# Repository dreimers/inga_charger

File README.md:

# inga_charger
Small device for (fast) charging INGA or compatible lipo batteries.

This devices uses [Microchips] (http://www.microchip.com) MCP73831 to
charge the single cell lipo batteries used 
for [inga] (http://ibr-cm.github.io/contiki-inga/)

It could also be used to charge other compatible lipo batteries.

##specifications
based on [MCP7831 Datasheet](http://www.microchip.com/wwwproducts/Devices.aspx?product=MCP73831)
- User-programmable charge current 15mA to 500mA
- Vsupply range 	3.75 to 6V

The part can be found in [my_eagle_parts] (https://github.com/dreimers/my_eagle_parts)

##schematic

##layout
###top

###bottom

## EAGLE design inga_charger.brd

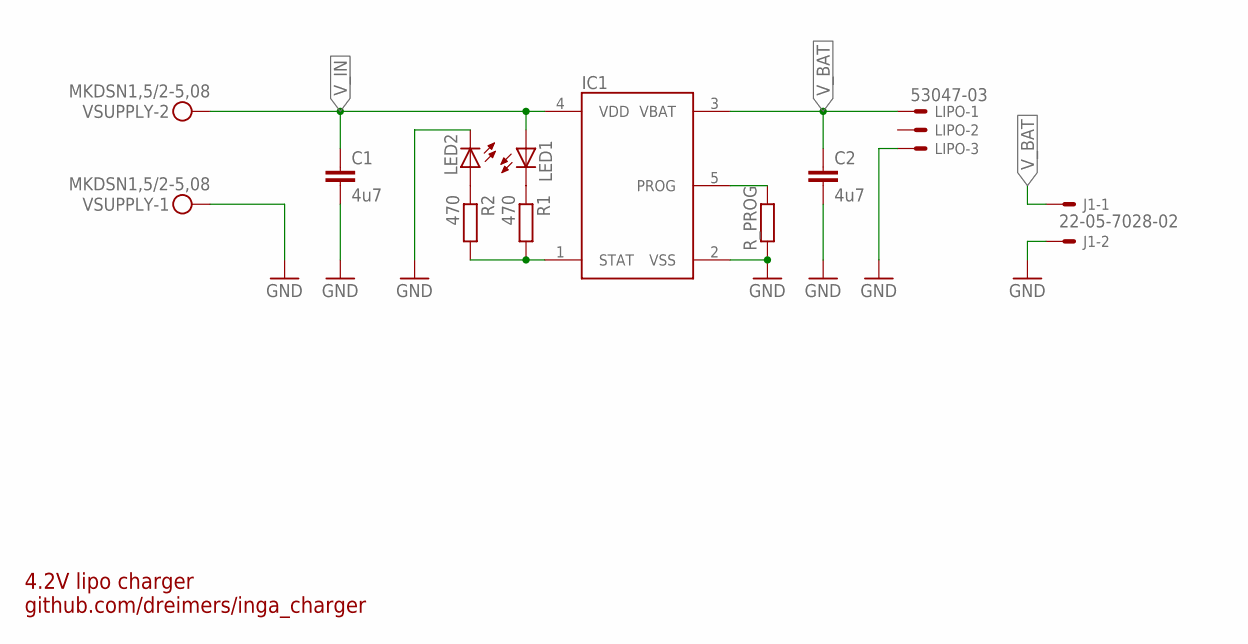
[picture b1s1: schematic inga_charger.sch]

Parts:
C1, C2: 4u7; C0805
IC1: MCP73831/2; SOT23-5
J1: 22-05-7028-02; 7395-02
LED1, LED2: LEDCHIP-LED0603; CHIP-LED0603
LIPO: 53047-03
R1, R2: 470; R0402
R_PROG: R-EU_R0603; R0603
VSUPPLY: MKDSN1,5/2-5,08

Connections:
GND: C1.2, C2.2, IC1.2 (VSS), J1.2, LED2.C, LIPO.3, R_PROG.1, VSUPPLY.1
unnamed: LED1.C, R1.1
unnamed: IC1.1 (STAT), R1.2, R2.2
unnamed: IC1.5 (PROG), R_PROG.2
unnamed: LED2.A, R2.1
V_BAT: C2.1, IC1.3 (VBAT), J1.1, LIPO.1
V_IN: C1.1, IC1.4 (VDD), LED1.A, VSUPPLY.2

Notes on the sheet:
4.2V lipo charger github.com/dreimers/inga_charger

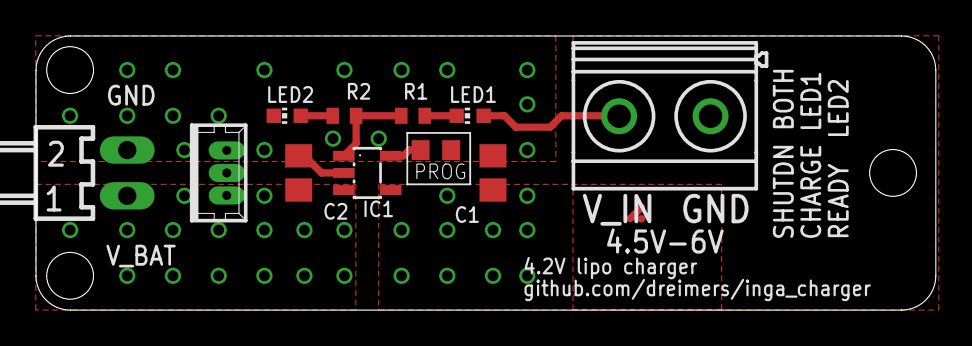
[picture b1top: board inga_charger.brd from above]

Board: 2 copper layers, 50.0 x 15.2 mm, 11 parts (0 on the bottom side), 7 nets.

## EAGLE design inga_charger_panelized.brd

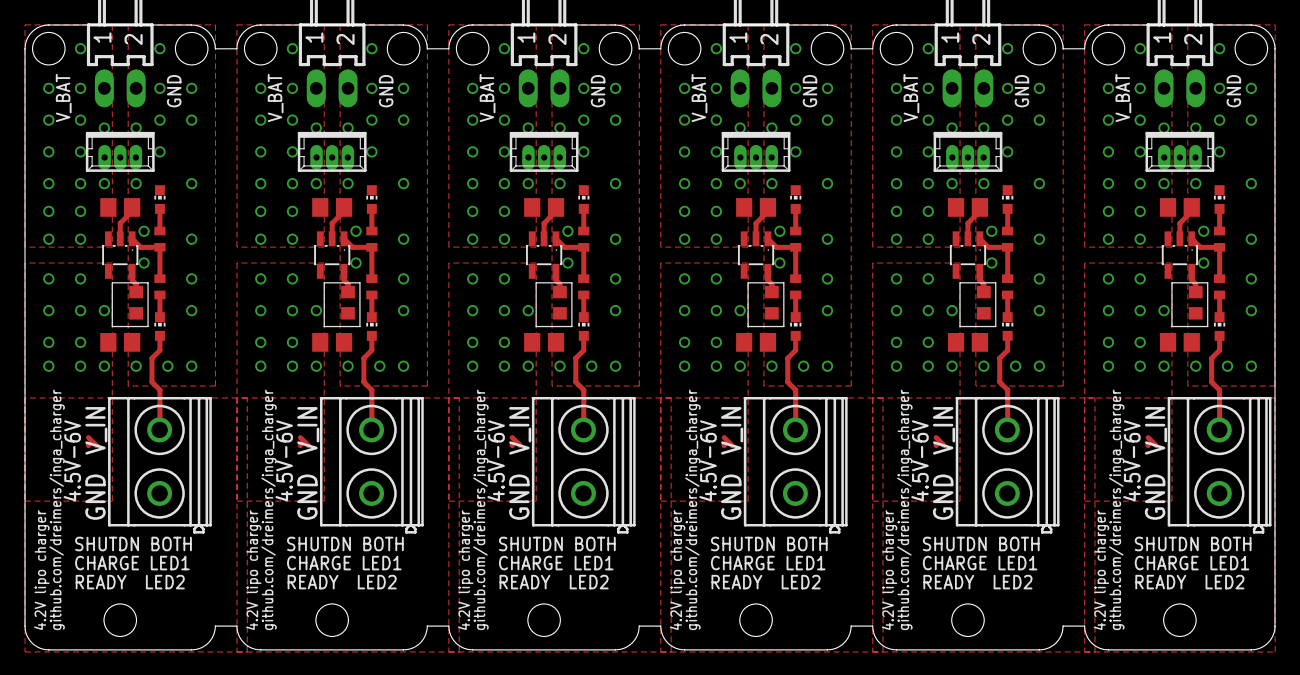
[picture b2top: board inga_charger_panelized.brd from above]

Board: 2 copper layers, 100.0 x 50.0 mm, 66 parts (0 on the bottom side), 32 nets.

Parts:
C1, C2, C3, C4, C5, C6, C7, C8, C9, C10, C11, C12: 4u7; C0805
IC1, IC2, IC3, IC4, IC5, IC6: SOT23-5
J1, J2, J3, J4, J5, J6: 22-05-7028-02; 7395-02
LED1, LED2, LED3, LED4, LED5, LED6, LED7, LED8, LED9, LED10, LED11, LED12: CHIP-LED0603
LIPO, LIPO1, LIPO2, LIPO3, LIPO4, LIPO5: 53047-03
PROG, PROG1, PROG2, PROG3, PROG4, PROG5: R0603
R1, R2, R3, R4, R5, R6, R7, R8, R9, R10, R11, R12: 470; R0402
VSUPPLY, VSUPPLY1, VSUPPLY2, VSUPPLY3, VSUPPLY4, VSUPPLY5: MKDSN1,5/2-5,08

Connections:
GND: C1.2, C2.2, C3.2, C4.2, C5.2, C6.2, C7.2, C8.2, C9.2, C10.2, C11.2, C12.2, IC1.2, IC2.2, IC3.2, IC4.2, IC5.2, IC6.2, J1.2, J2.2, J3.2, J4.2, J5.2, J6.2, LED2.C, LED4.C, LED6.C, LED8.C, LED10.C, LED12.C, LIPO.3, LIPO1.3, LIPO2.3, LIPO3.3, LIPO4.3, LIPO5.3, PROG.1, PROG1.1, PROG2.1, PROG3.1, PROG4.1, PROG5.1, VSUPPLY.1, VSUPPLY1.1, VSUPPLY2.1, VSUPPLY3.1, VSUPPLY4.1, VSUPPLY5.1
unnamed: LED1.C, R1.1
unnamed: IC1.1, R1.2, R5.2
unnamed: LED3.C, R2.1
unnamed: IC1.5, PROG.2
unnamed: LED2.A, R5.1
unnamed: IC2.1, R2.2, R3.2
unnamed: IC2.5, PROG1.2
unnamed: LED4.A, R3.1
unnamed: LED5.C, R4.1
unnamed: IC3.1, R4.2, R6.2
unnamed: IC3.5, PROG2.2
unnamed: LED6.A, R6.1
unnamed: LED7.C, R7.1
unnamed: IC4.1, R7.2, R8.2
unnamed: IC4.5, PROG3.2
unnamed: LED8.A, R8.1
unnamed: LED9.C, R9.1
unnamed: IC5.1, R9.2, R10.2
unnamed: IC5.5, PROG4.2
unnamed: LED10.A, R10.1
unnamed: LED11.C, R11.1
unnamed: IC6.1, R11.2, R12.2
unnamed: IC6.5, PROG5.2
unnamed: LED12.A, R12.1
V_BAT: C2.1, IC1.3, J1.1, LIPO.1
V_BAT1: C4.1, IC2.3, J2.1, LIPO1.1
V_BAT2: C6.1, IC3.3, J3.1, LIPO2.1
V_BAT3: C8.1, IC4.3, J4.1, LIPO3.1
V_BAT4: C10.1, IC5.3, J5.1, LIPO4.1
V_BAT5: C12.1, IC6.3, J6.1, LIPO5.1
V_IN: C1.1, C3.1, C5.1, C7.1, C9.1, C11.1, IC1.4, IC2.4, IC3.4, IC4.4, IC5.4, IC6.4, LED1.A, LED3.A, LED5.A, LED7.A, LED9.A, LED11.A, VSUPPLY.2, VSUPPLY1.2, VSUPPLY2.2, VSUPPLY3.2, VSUPPLY4.2, VSUPPLY5.2

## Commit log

2015-04-24 Update README.md
    More description like specs and links to related documentation
2015-04-24 Adds first draft of schematic
    NOTE: Not ready for production
2015-04-24 Adds first draft of board
    NOTE: Not ready for production
2015-05-08 Adds new version of board and schematic
2015-05-08 Adds gitignore list for eagle
2015-05-08 Adds panelized version of the board
2015-05-08 Adds pdf exports of schematic and board
2015-05-13 Adds image of pcb and schematic to docs
2015-05-13 Update README.md
    Adds schematic and pcb images
